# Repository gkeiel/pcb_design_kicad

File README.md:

# Printed circuit board designs

A repository with **designs of printed circuit boards (PCBs)** for electronic circuits developed with KiCad. Each project has its own folder, focused on a different and specific problem.

The following projects are available:
- [full-bridge DC driver Arduino Nano (carrier board)](./arduino_nano_fullbridge_dc_driver)
- [low-side DC driver Arduino Nano (carrier board)](./arduino_nano_low_side_dc_driver)
- [relay module 5 V optocoupler SMT 4 channels](./relay_module_5v_optocoupler_4_smt)
- [relay module 5 V optocoupler SMT](./relay_module_5v_optocoupler_smt)
- [power supply with linear regulator 78xx](./power_supply_linear_regulator_78xx)
- [power supply with linear regulator lm317](./power_supply_linear_regulator_lm317)

## Arduino Nano full-bridge DC and sensor
A PCB design to a carrier board for Arduino Nano with full-bridge circuit and voltage sensors.

## Arduino Nano low-side DC driver and sensor
A PCB design to a carrier board for Arduino Nano with 2 low-side switches and voltage sensors.

## Relay module 3.3/5/12 V optocoupler SMT 4 channels
A two-layer PCB design to a four-channel relay module with optocoupler.

## Relay module 3.3/5/12 V optocoupler SMT
A two-layer PCB design to a single-channel relay module with optocoupler.

## Premium version

This repository contains **open versions** which consider single-sided 1oz boards and Through-Hole Technology (THT) for components. Improved designs or boards using Surface Mount Technology (SMT) can be developed on request.

**Premium versions**, with additional features, extended documentation and support, are available at:  
👉 https://payhip.com/gkeiel

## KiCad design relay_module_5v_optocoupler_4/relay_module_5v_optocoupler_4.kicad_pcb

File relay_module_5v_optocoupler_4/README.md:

# Relay module 5V optocoupler 4 channels

PCB design of a four-channel 5V relay module with optocoupler:

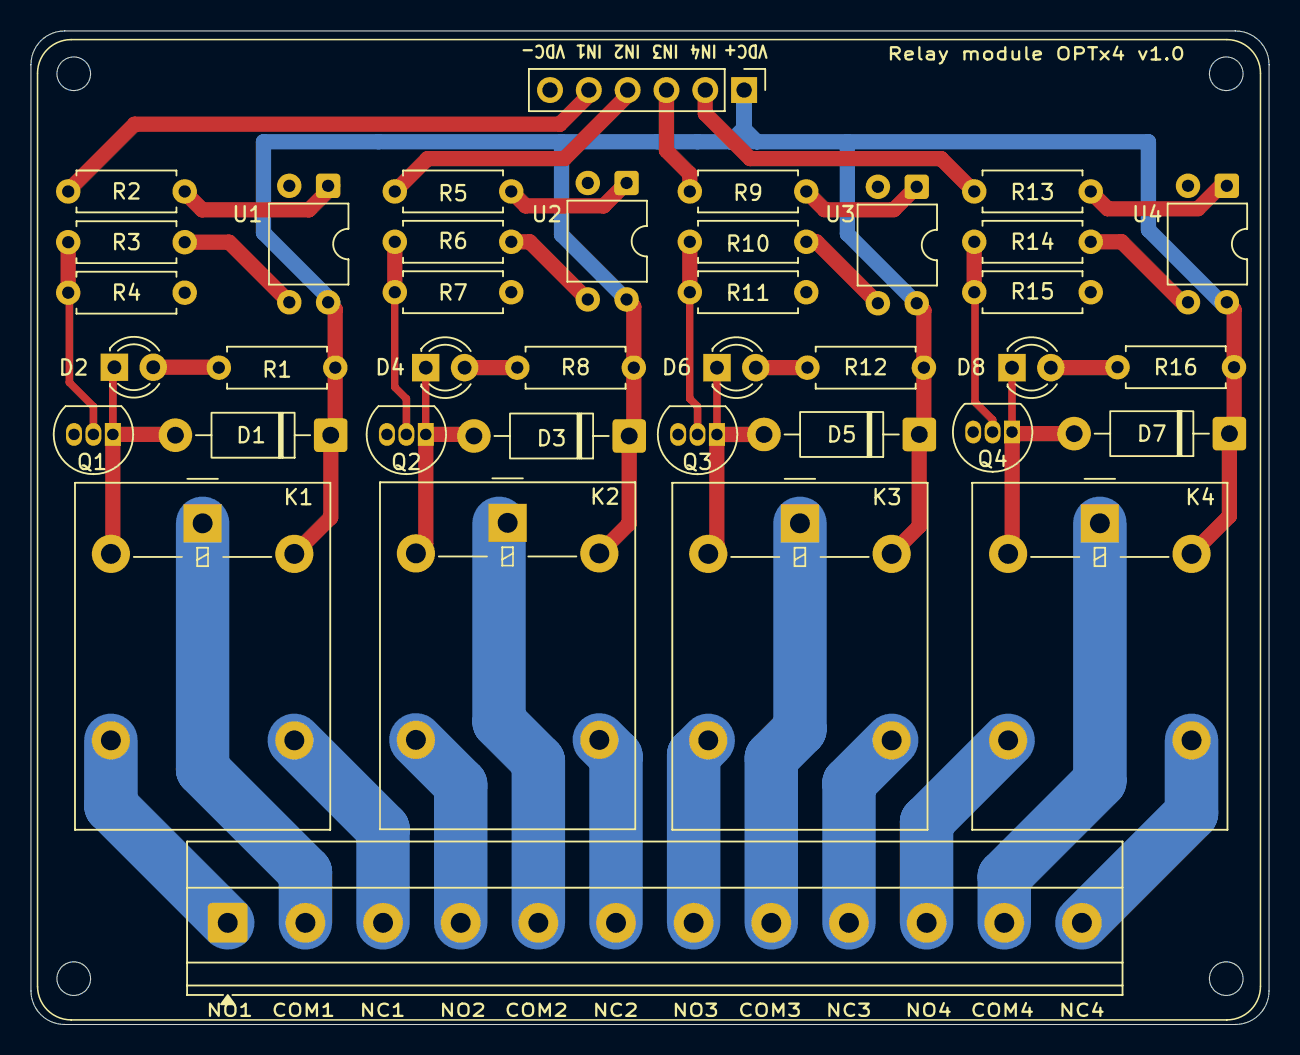
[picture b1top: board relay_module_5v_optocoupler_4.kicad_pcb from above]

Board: 2 copper layers, 81.0 x 65.0 mm, 38 parts (0 on the bottom side), 38 nets.

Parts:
D1, D3, D5, D7: 1N4007; D_DO-41_SOD81_P10.16mm_Horizontal
D2, D4, D6, D8: LED; LED_D3.0mm
J1: Conn_01x02_Pin; PinHeader_1x06_P2.54mm_Vertical
J2: Conn_01x03_Pin; TerminalBlock_Phoenix_MKDS-1,5-12-5.08_1x12_P5.08mm_Horizon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
K1, K2, K3, K4: Relay_SPDT; Relay_SPDT_Omron-G5LE-1
Q1, Q2, Q3, Q4: BC337; TO-92_Inline
R1, R2, R3, R4, R5, R6, R7, R8, R9, R10, R11, R12, R13, R14, R15, R16: R; R_Axial_DIN0207_L6.3mm_D2.5mm_P7.62mm_Horizontal
U1, U2, U3, U4: PC817; DIP-4_W7.62mm

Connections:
C_1: J2.2, K1.3
C_2: J2.5, K2.3
C_3: J2.8, K3.3
C_4: J2.11, K4.3
GND: J1.6, Q1.3 (E), Q2.3 (E), Q3.3 (E), Q4.3 (E), R4.1, R7.1, R11.1, R15.1, U1.2, U2.2, U3.2, U4.2
IN1: J1.5, R2.1
IN2: J1.4, R5.1
IN3: J1.3, R9.1
IN4: J1.2, R13.1
NC_1: J2.3, K1.4
NC_2: J2.6, K2.4
NC_3: J2.9, K3.4
NC_4: J2.12, K4.4
NO_1: J2.1, K1.5
NO_2: J2.4, K2.5
NO_3: J2.7, K3.5
NO_4: J2.10, K4.5
unnamed: D1.2 (A), D2.1 (K), K1.2, Q1.1 (C)
unnamed: D2.2 (A), R1.2
unnamed: D3.2 (A), D4.1 (K), K2.2, Q2.1 (C)
unnamed: D4.2 (A), R8.2
unnamed: D5.2 (A), D6.1 (K), K3.2, Q3.1 (C)
unnamed: D6.2 (A), R12.2
unnamed: D7.2 (A), D8.1 (K), K4.2, Q4.1 (C)
unnamed: D8.2 (A), R16.2
unnamed: Q1.2 (B), R3.2, R4.2
unnamed: Q2.2 (B), R6.2, R7.2
unnamed: Q3.2 (B), R10.2, R11.2
unnamed: Q4.2 (B), R14.2, R15.2
unnamed: R2.2, U1.1
unnamed: R3.1, U1.3
unnamed: R5.2, U2.1
unnamed: R6.1, U2.3
unnamed: R9.2, U3.1
unnamed: R10.1, U3.3
unnamed: R13.2, U4.1
unnamed: R14.1, U4.3
VDC+: D1.1 (K), D3.1 (K), D5.1 (K), D7.1 (K), J1.1, K1.1, K2.1, K3.1, K4.1, R1.1, R8.1, R12.1, R16.1, U1.4, U2.4, U3.4, U4.4

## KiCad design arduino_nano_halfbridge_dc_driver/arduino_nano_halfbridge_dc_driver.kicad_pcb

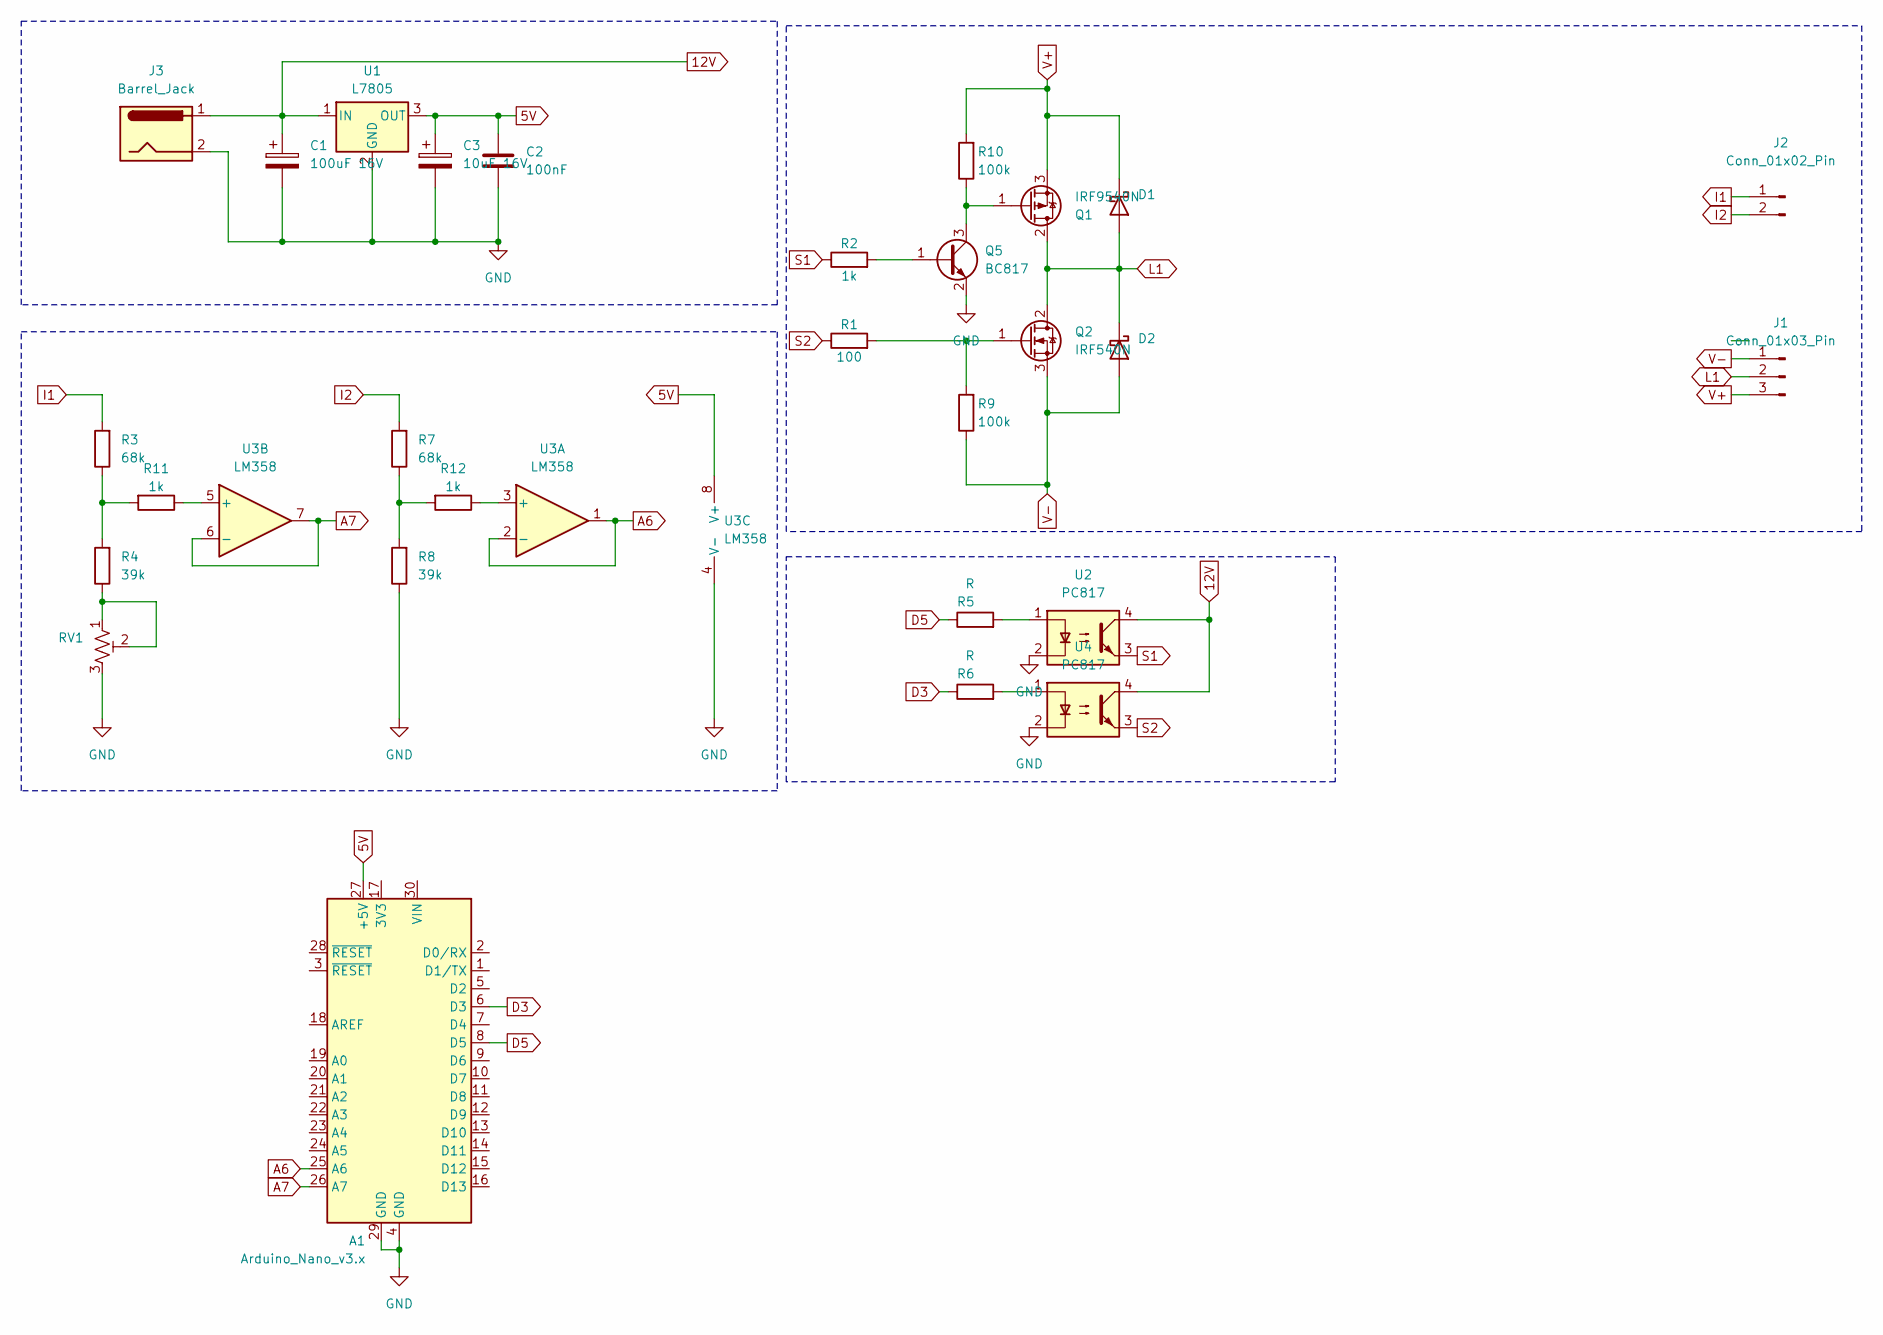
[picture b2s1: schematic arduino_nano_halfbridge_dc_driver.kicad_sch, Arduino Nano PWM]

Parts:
A1: Arduino_Nano_v3.x; Arduino_Nano
C1: 100uF 16V; CP_Elec_6.3x5.4
C2: 100nF; C_0603_1608Metric
C3: 10uF 16V; CP_Elec_6.3x5.4
D1, D2: B120-E3; D_SMC
J1: Conn_01x03_Pin; TerminalBlock_Phoenix_MKDS-1,5-3-5.08_1x03_P5.08mm_Horizont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
J2: Conn_01x02_Pin; PinHeader_1x02_P2.54mm_Vertical
J3: Barrel_Jack; BarrelJack_Horizontal
Q1: IRF9540N; TO-220-3_Horizontal_TabDown
Q2: IRF540N; TO-220-3_Horizontal_TabDown
Q5: BC817; SOT-23
R1: 100; R_0805_2012Metric
R2, R11, R12: 1k; R_0805_2012Metric
R3, R7: 68k; R_0805_2012Metric
R4, R8: 39k; R_0805_2012Metric
R5, R6: R; R_0805_2012Metric
R9, R10: 100k; R_0805_2012Metric
RV1: R_Potentiometer_Trim_US; Potentiometer_Bourns_3296W_Vertical
U1: L7805; TO-252-2
U2, U4: PC817; SO-4_4.4x3.6mm_P2.54mm
U3: LM358; SOIC-8_3.9x4.9mm_P1.27mm

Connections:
5V: A1.27 (+5V), C2.1, C3.1, U1.3 (OUT), U3.8 (V+)
12V: C1.1, J3.1, U1.1 (IN), U2.4, U4.4
A6: A1.25 (A6), U3.1, U3.2 (-)
A7: A1.26 (A7), U3.6 (-), U3.7
D3: A1.6 (D3), R6.1
D5: A1.8 (D5), R5.1
GND: A1.4 (GND), A1.29 (GND), C1.2, C2.2, C3.2, J3.2, Q5.2 (E), R8.1, RV1.3, U1.2 (GND), U2.2, U3.4 (V-), U4.2; also elsewhere on the board
I1: J2.1, R3.2
I2: J2.2, R7.2
L1: D1.2 (A), D2.1 (K), J1.2, Q1.2 (D), Q2.2 (D)
unnamed: Q1.1 (G), Q5.3 (C), R10.1
unnamed: Q2.1 (G), R1.2, R9.2
unnamed: Q5.1 (B), R2.2
unnamed: R4.1, RV1.1, RV1.2
unnamed: R5.2, U2.1
unnamed: R6.2, U4.1
unnamed: R3.1, R4.2, R11.2
unnamed: R7.1, R8.2, R12.2
unnamed: R12.1, U3.3 (+)
unnamed: R11.1, U3.5 (+)
S1: R2.1, U2.3; also elsewhere on the board
S2: R1.1, U4.3; also elsewhere on the board
V+: D1.1 (K), J1.3, Q1.3 (S), R10.2
V-: D2.2 (A), J1.1, Q2.3 (S), R9.1

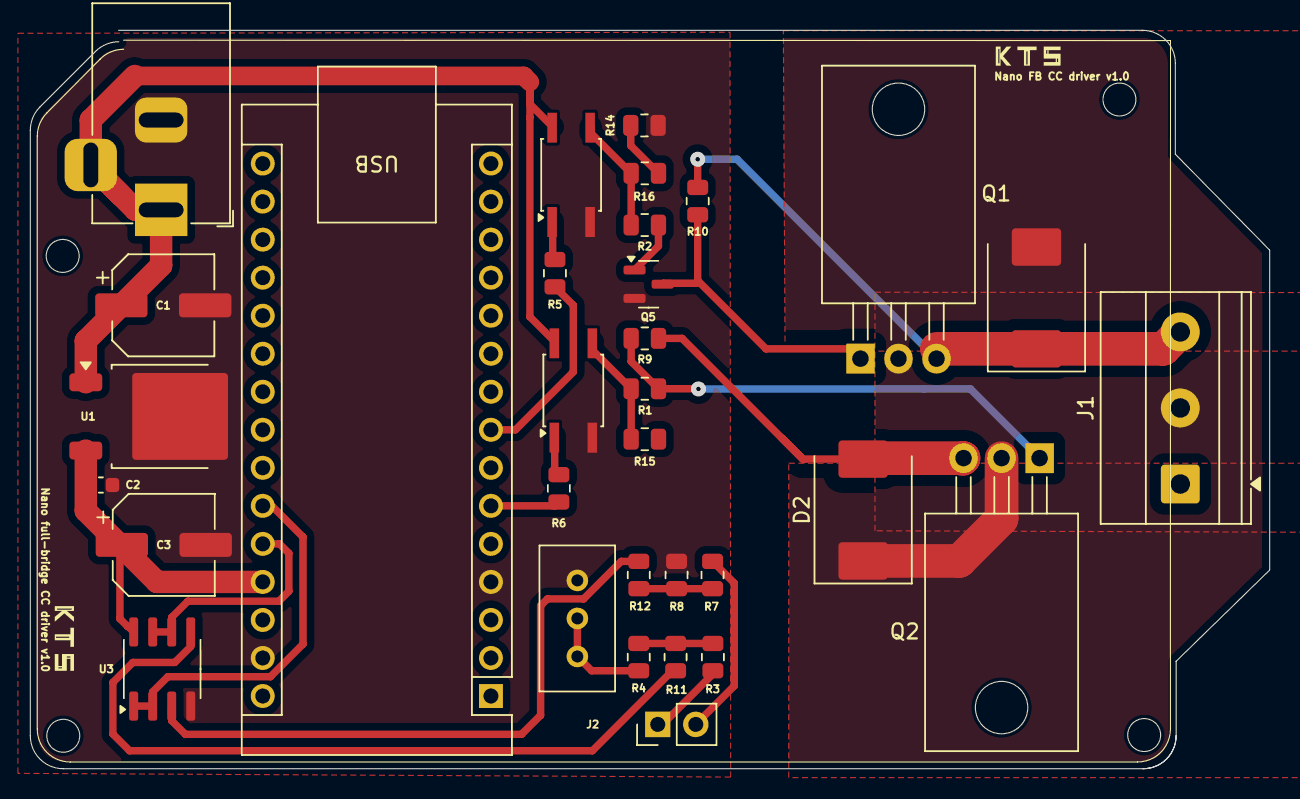
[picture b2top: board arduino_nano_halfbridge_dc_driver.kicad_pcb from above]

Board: 2 copper layers, 82.8 x 49.3 mm, 32 parts (0 on the bottom side), 25 nets.

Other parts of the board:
R14: 100k; R_0805_2012Metric
R15: 1k; R_0805_2012Metric
R16: 100; R_0805_2012Metric

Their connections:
GND: R14.1; also elsewhere on the board
unnamed: R14.2, R16.2
S1: R16.1; also elsewhere on the board
S2: R15.1; also elsewhere on the board

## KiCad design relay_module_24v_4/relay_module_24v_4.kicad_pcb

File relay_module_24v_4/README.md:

# Relay module 24V 4 channels

PCB design of a four-channel 24V relay module.

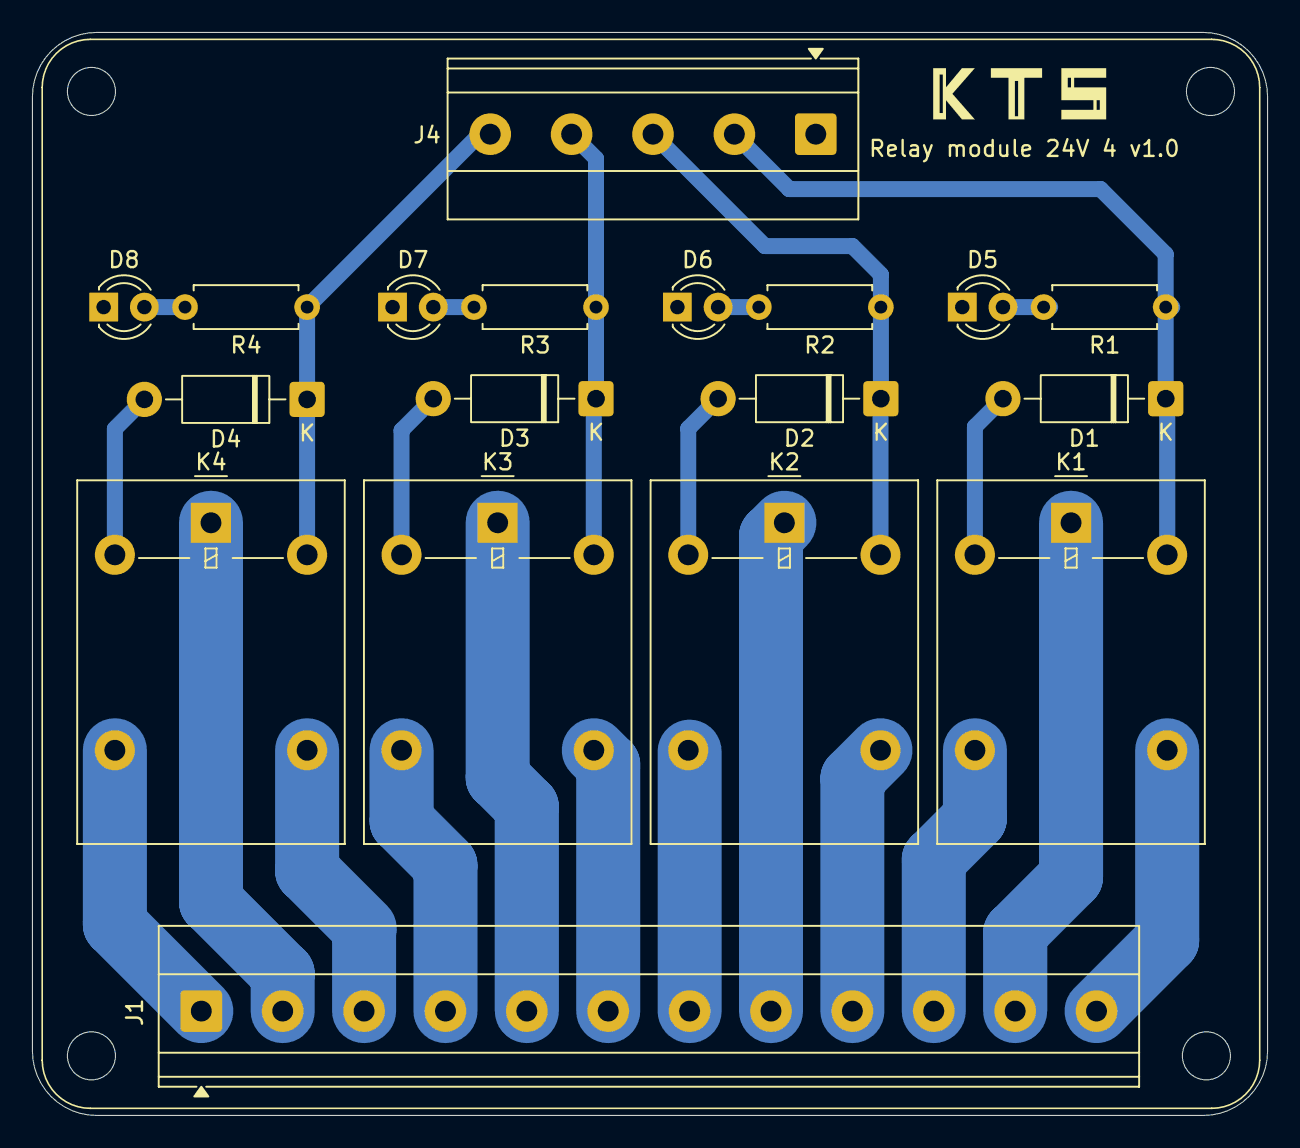
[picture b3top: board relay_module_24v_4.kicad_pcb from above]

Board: 2 copper layers, 77.1 x 67.6 mm, 18 parts (0 on the bottom side), 21 nets.

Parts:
D1, D2, D3, D4: 1N4007; D_DO-41_SOD81_P10.16mm_Horizontal
D5, D6, D7, D8: LED; LED_D3.0mm
J1: Conn_01x12_Pin; TerminalBlock_Phoenix_MKDS-1,5-12-5.08_1x12_P5.08mm_Horizon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
J4: Conn_01x05_Pin; TerminalBlock_Phoenix_MKDS-1,5-5-5.08_1x05_P5.08mm_Horizont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
K1, K2, K3, K4: Relay_SPDT; Relay_SPDT_Omron-G5LE-1
R1, R2, R3, R4: R; R_Axial_DIN0207_L6.3mm_D2.5mm_P7.62mm_Horizontal

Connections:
C_1: J1.11, K1.3
C_2: J1.8, K2.3
C_3: J1.5, K3.3
C_4: J1.2, K4.3
GND: D1.2 (A), D2.2 (A), D3.2 (A), D4.2 (A), D5.1 (K), D6.1 (K), D7.1 (K), D8.1 (K), J4.1, K1.2, K2.2, K3.2, K4.2
NC_1: J1.12, K1.4
NC_2: J1.9, K2.4
NC_3: J1.6, K3.4
NC_4: J1.3, K4.4
NO_1: J1.10, K1.5
NO_2: J1.7, K2.5
NO_3: J1.4, K3.5
NO_4: J1.1, K4.5
unnamed: D1.1 (K), J4.2, K1.1, R1.1
unnamed: D2.1 (K), J4.3, K2.1, R2.1
unnamed: D3.1 (K), J4.4, K3.1, R3.1
unnamed: D4.1 (K), J4.5, K4.1, R4.1
unnamed: D5.2 (A), R1.2
unnamed: D6.2 (A), R2.2
unnamed: D7.2 (A), R3.2
unnamed: D8.2 (A), R4.2

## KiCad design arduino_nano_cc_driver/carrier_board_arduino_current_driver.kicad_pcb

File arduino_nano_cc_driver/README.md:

# Arduino Nano continuous current (CC) driver and sensor

PCB design of a carrier board for Arduino Nano with PWM switches and sensor.

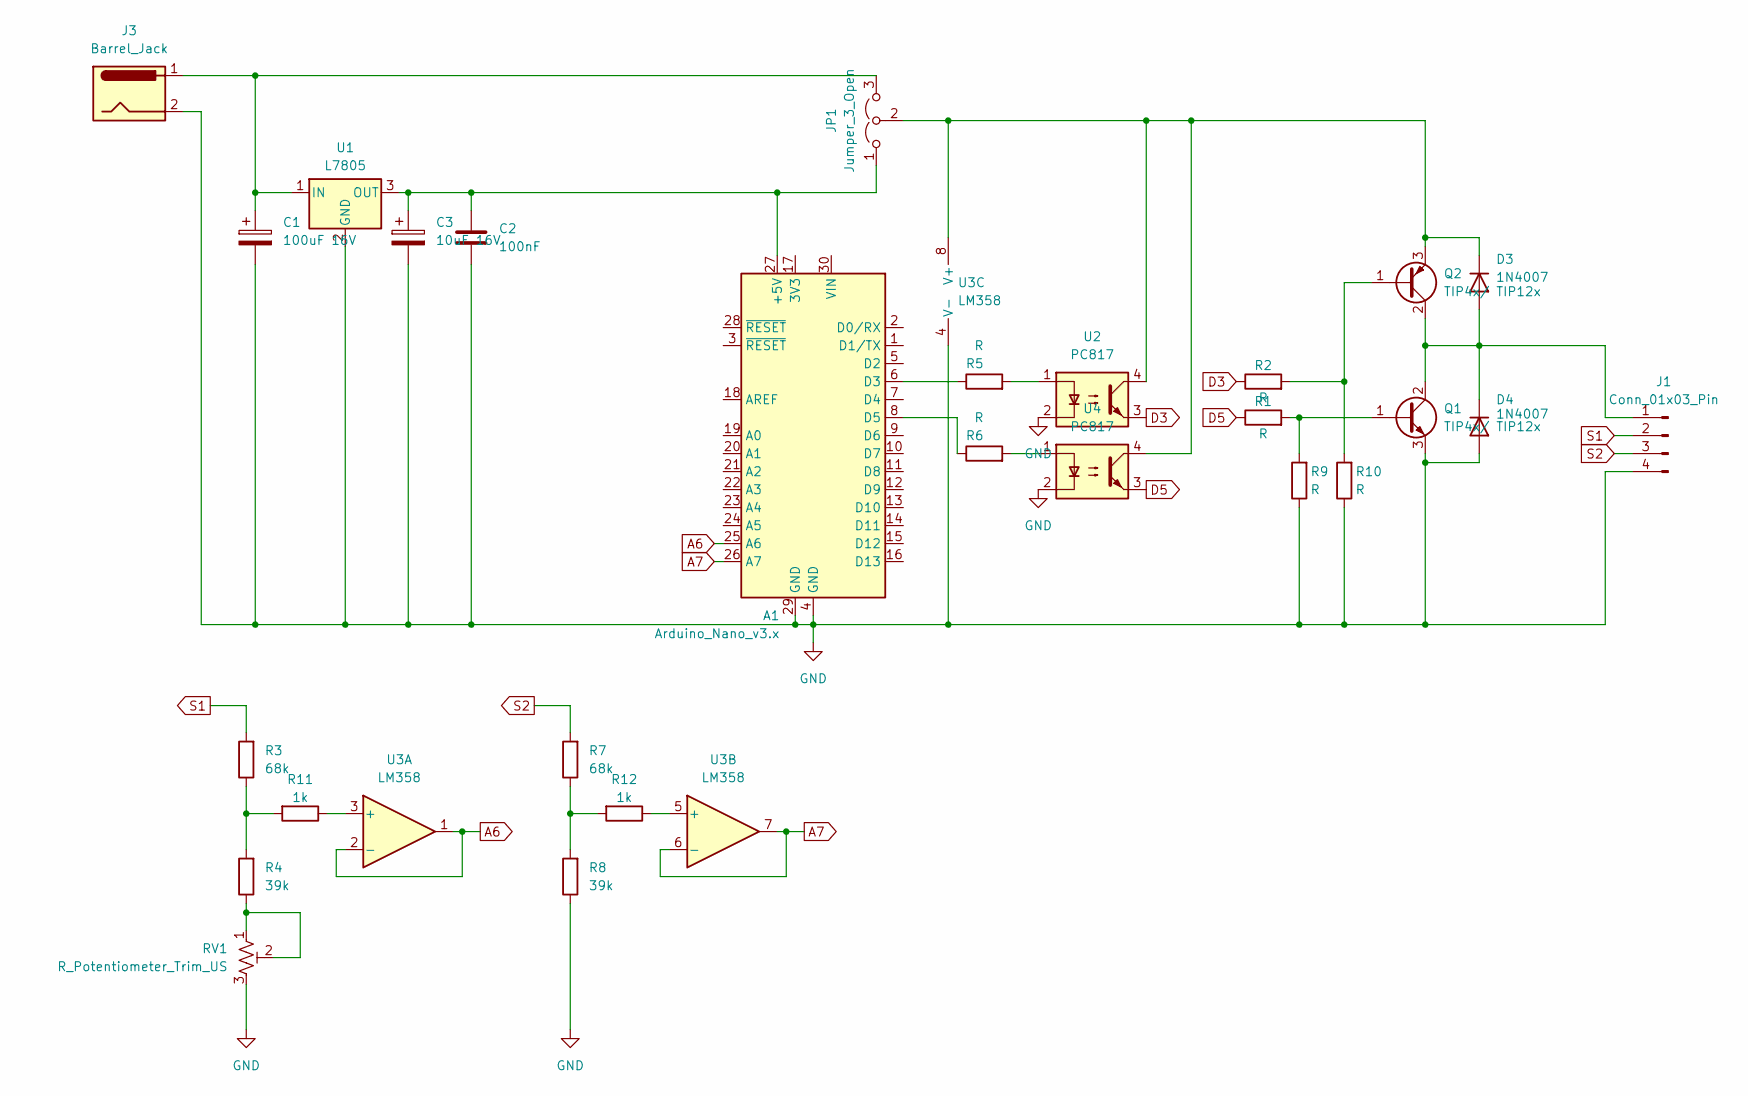
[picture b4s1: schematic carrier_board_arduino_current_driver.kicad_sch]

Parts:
A1: Arduino_Nano_v3.x; Arduino_Nano
C1: 100uF 16V; CP_Elec_6.3x5.4
C2: 100nF; C_0603_1608Metric
C3: 10uF 16V; CP_Elec_6.3x5.4
D3, D4: 1N4007; D_SOD-123
J1: Conn_01x03_Pin; PinHeader_1x04_P2.54mm_Vertical
J3: Barrel_Jack; BarrelJack_Horizontal
JP1: Jumper_3_Open; PinHeader_1x03_P2.54mm_Vertical
Q1, Q2: TIP4x/ TIP12x; TO-220-3_Vertical
R1, R2, R5, R6, R9, R10: R; R_0805_2012Metric
R3, R7: 68k; R_0805_2012Metric
R4, R8: 39k; R_0805_2012Metric
R11, R12: 1k; R_0805_2012Metric
RV1: R_Potentiometer_Trim_US; Potentiometer_Bourns_3296W_Vertical
U1: L7805; TO-252-2
U2, U4: PC817; SO-4_4.4x3.6mm_P2.54mm
U3: LM358; SOIC-8_3.9x4.9mm_P1.27mm

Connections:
A6: A1.25 (A6), U3.1, U3.2 (-)
A7: A1.26 (A7), U3.6 (-), U3.7
D3: R2.1, U2.3
D5: R1.1, U4.3
GND: A1.4 (GND), A1.29 (GND), C1.2, C2.2, C3.2, D4.2 (A), J1.4, J3.2, Q1.3 (E), R8.1, R9.1, R10.1, RV1.3, U1.2 (GND), U2.2, U3.4 (V-), U4.2
unnamed: A1.27 (+5V), C2.1, C3.1, JP1.1 (A), U1.3 (OUT)
unnamed: A1.6 (D3), R5.1
unnamed: A1.8 (D5), R6.1
unnamed: D3.2 (A), D4.1 (K), J1.1, Q1.2 (C), Q2.2 (C)
unnamed: D3.1 (K), JP1.2 (C), Q2.3 (E), U2.4, U3.8 (V+), U4.4
unnamed: C1.1, J3.1, JP1.3 (B), U1.1 (IN)
unnamed: Q1.1 (B), R1.2, R9.2
unnamed: Q2.1 (B), R2.2, R10.2
unnamed: R4.1, RV1.1, RV1.2
unnamed: R5.2, U2.1
unnamed: R6.2, U4.1
unnamed: R3.1, R4.2, R11.2
unnamed: R7.1, R8.2, R12.2
unnamed: R11.1, U3.3 (+)
unnamed: R12.1, U3.5 (+)
S1: J1.2, R3.2
S2: J1.3, R7.2

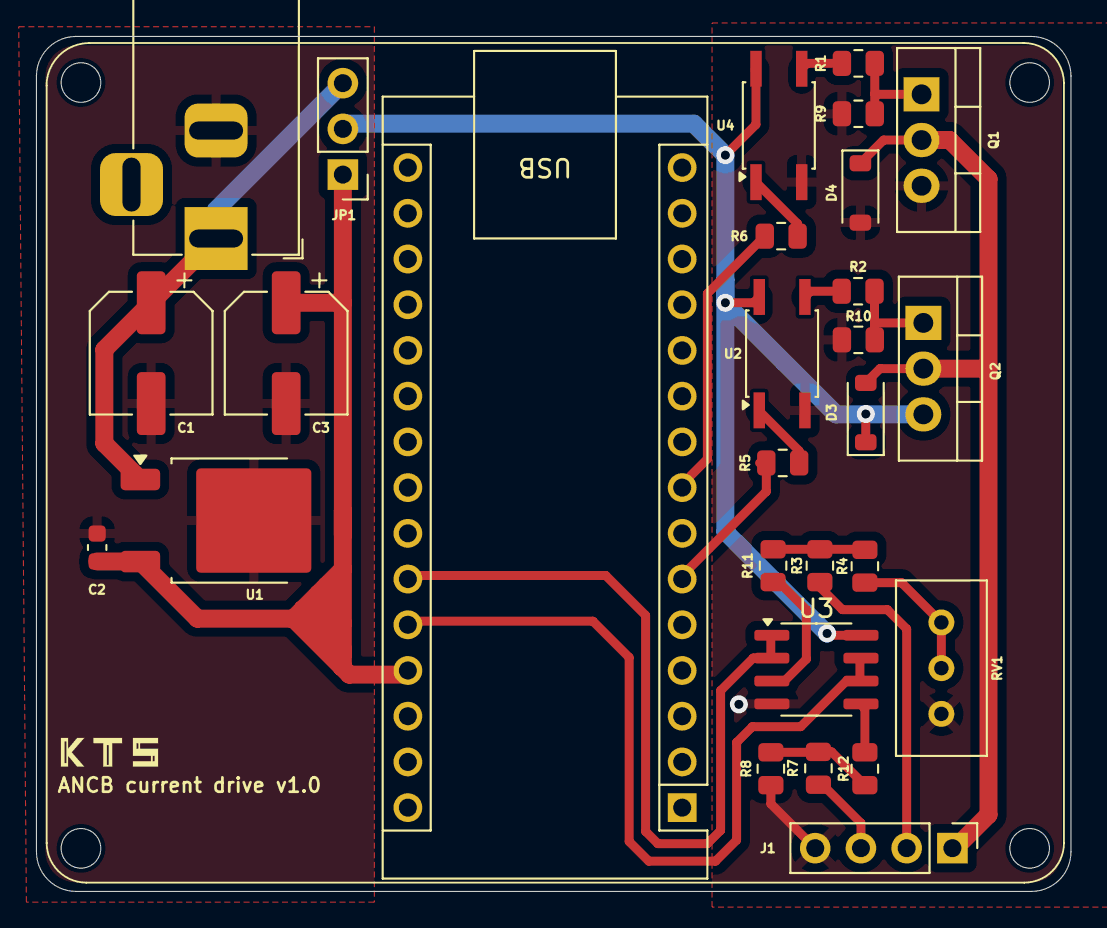
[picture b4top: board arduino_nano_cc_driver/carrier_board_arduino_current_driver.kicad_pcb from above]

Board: 2 copper layers, 57.5 x 47.5 mm, 28 parts (0 on the bottom side), 22 nets.

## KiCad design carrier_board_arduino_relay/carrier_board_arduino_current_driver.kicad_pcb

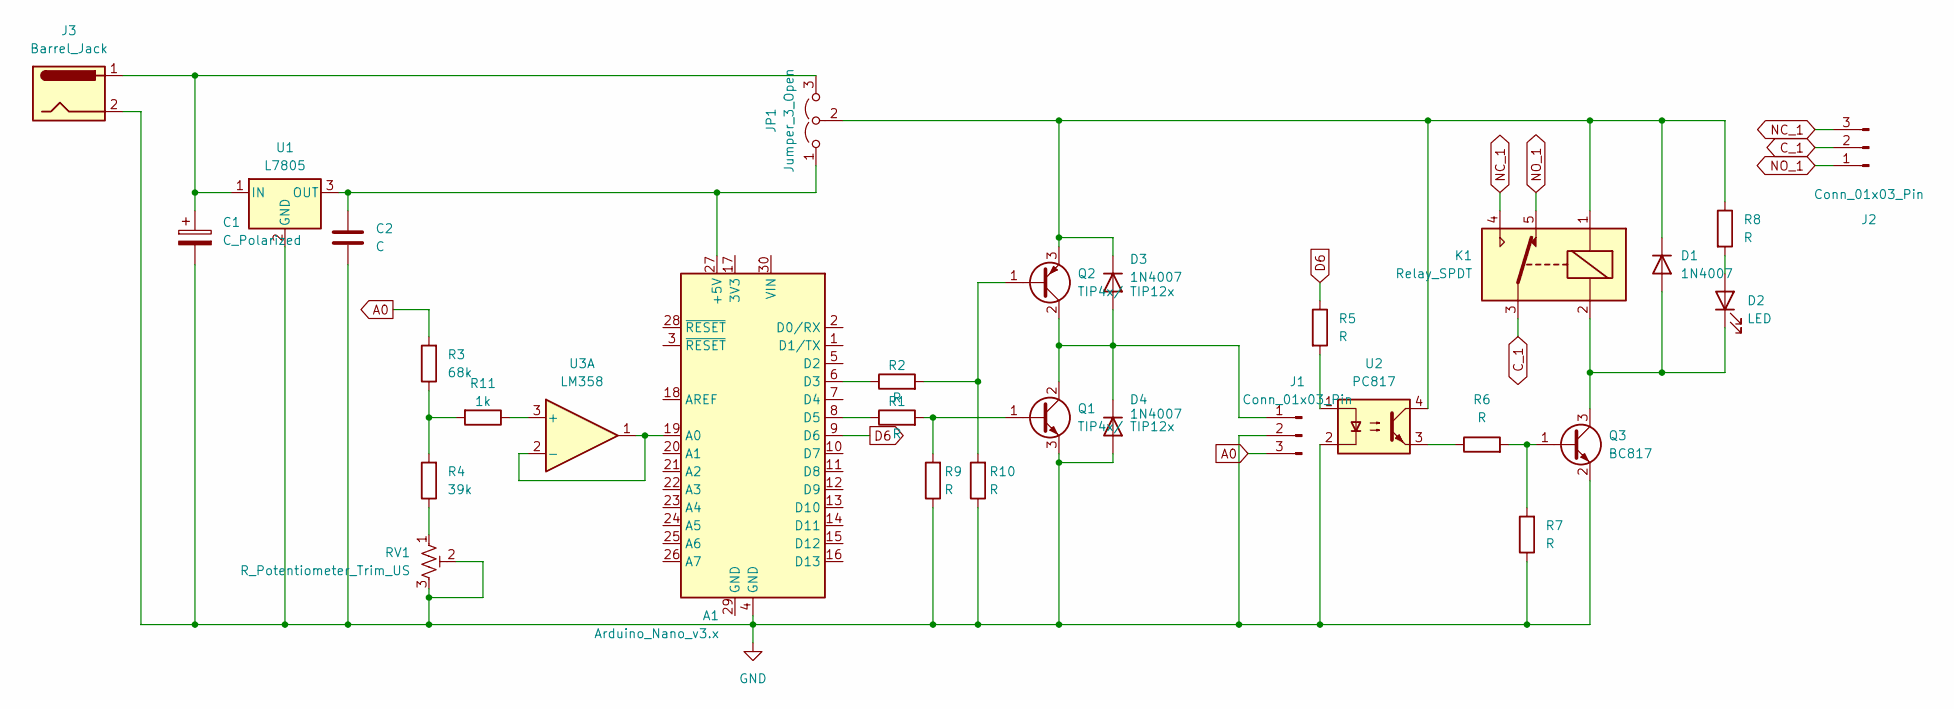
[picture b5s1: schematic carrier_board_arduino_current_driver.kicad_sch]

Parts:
A1: Arduino_Nano_v3.x; Arduino_Nano
C1: C_Polarized; CP_Radial_D6.3mm_P2.50mm
C2: C; C_Disc_D5.0mm_W2.5mm_P5.00mm
D1, D3, D4: 1N4007; D_SOD-123
D2: LED; LED_0805_2012Metric
J1: Conn_01x03_Pin; PinHeader_1x03_P2.54mm_Vertical
J2: Conn_01x03_Pin; TerminalBlock_Phoenix_MKDS-1,5-3-5.08_1x03_P5.08mm_Horizont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
J3: Barrel_Jack; BarrelJack_Horizontal
JP1: Jumper_3_Open; PinHeader_1x03_P2.54mm_Vertical
K1: Relay_SPDT; Relay_SPDT_Omron-G5LE-1
Q1, Q2: TIP4x/ TIP12x; TO-220-3_Vertical
Q3: BC817; SOT-23
R1, R2, R5, R6, R7, R8, R9, R10: R; R_0805_2012Metric
R3: 68k; R_0805_2012Metric
R4: 39k; R_0805_2012Metric
R11: 1k; R_0805_2012Metric
RV1: R_Potentiometer_Trim_US; Potentiometer_Bourns_3296W_Vertical
U1: L7805; TO-252-2
U2: PC817; DIP-4_W7.62mm
U3: LM358; SOIC-8_3.9x4.9mm_P1.27mm

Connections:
A0: J1.3, R3.2
C_1: J2.2, K1.3
D6: A1.9 (D6), R5.1
GND: A1.4 (GND), C1.2, C2.2, D4.2 (A), J1.2, J3.2, Q1.3 (E), Q3.2 (E), R7.1, R9.1, R10.1, RV1.2, RV1.3, U1.2 (GND), U2.2
NC_1: J2.3, K1.4
NO_1: J2.1, K1.5
unnamed: A1.27 (+5V), C2.1, JP1.1 (A), U1.3 (OUT)
unnamed: A1.19 (A0), U3.1, U3.2 (-)
unnamed: A1.6 (D3), R2.1
unnamed: A1.8 (D5), R1.1
unnamed: D1.2 (A), D2.1 (K), K1.2, Q3.3 (C)
unnamed: D1.1 (K), D3.1 (K), JP1.2 (C), K1.1, Q2.3 (E), R8.1, U2.4
unnamed: D2.2 (A), R8.2
unnamed: D3.2 (A), D4.1 (K), J1.1, Q1.2 (C), Q2.2 (C)
unnamed: C1.1, J3.1, JP1.3 (B), U1.1 (IN)
unnamed: Q1.1 (B), R1.2, R9.2
unnamed: Q2.1 (B), R2.2, R10.2
unnamed: Q3.1 (B), R6.2, R7.2
unnamed: R4.1, RV1.1
unnamed: R5.2, U2.1
unnamed: R6.1, U2.3
unnamed: R3.1, R4.2, R11.2
unnamed: R11.1, U3.3 (+)

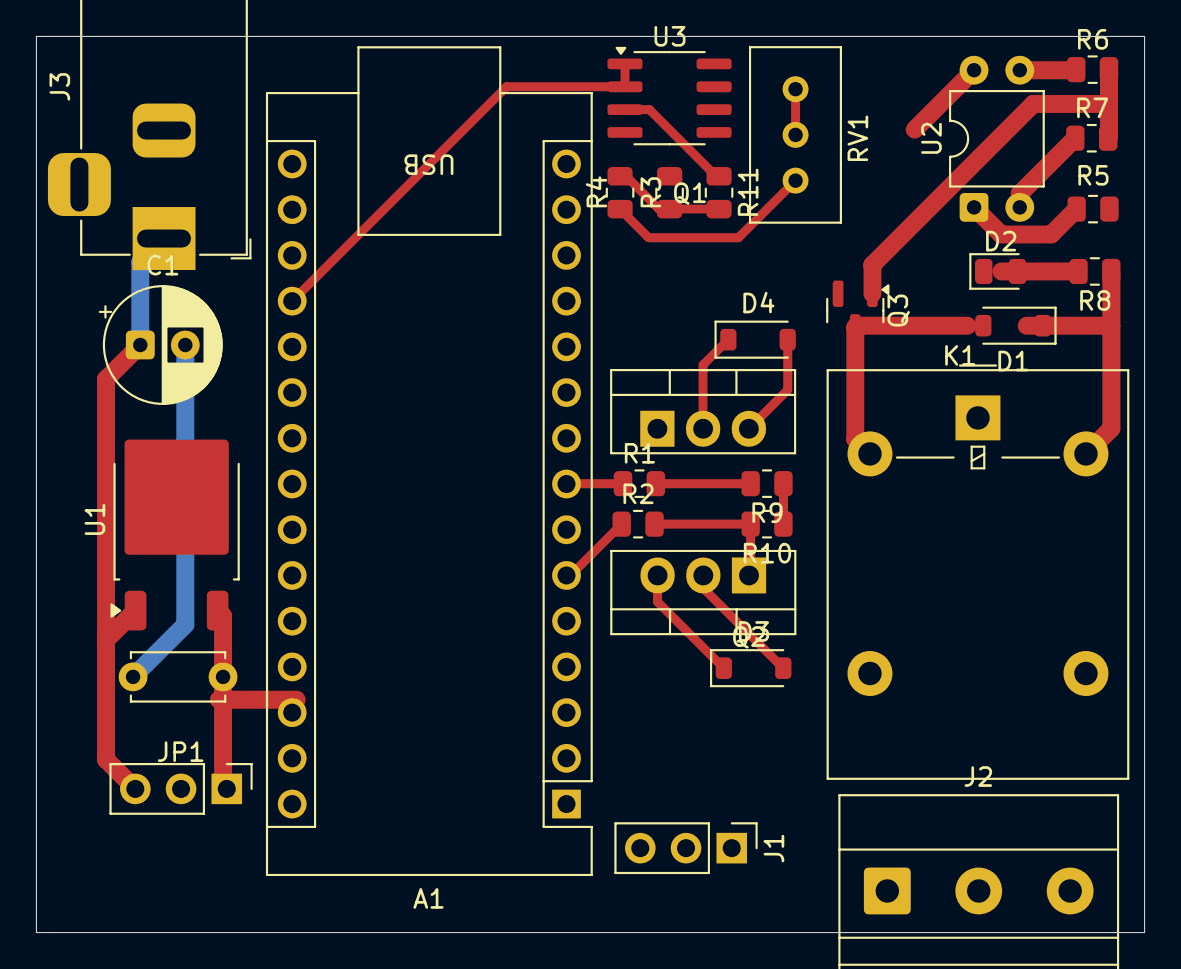
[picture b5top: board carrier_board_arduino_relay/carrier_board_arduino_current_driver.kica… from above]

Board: 2 copper layers, 61.6 x 49.8 mm, 30 parts (0 on the bottom side), 23 nets.

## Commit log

2026-01-29 v1.0.0
